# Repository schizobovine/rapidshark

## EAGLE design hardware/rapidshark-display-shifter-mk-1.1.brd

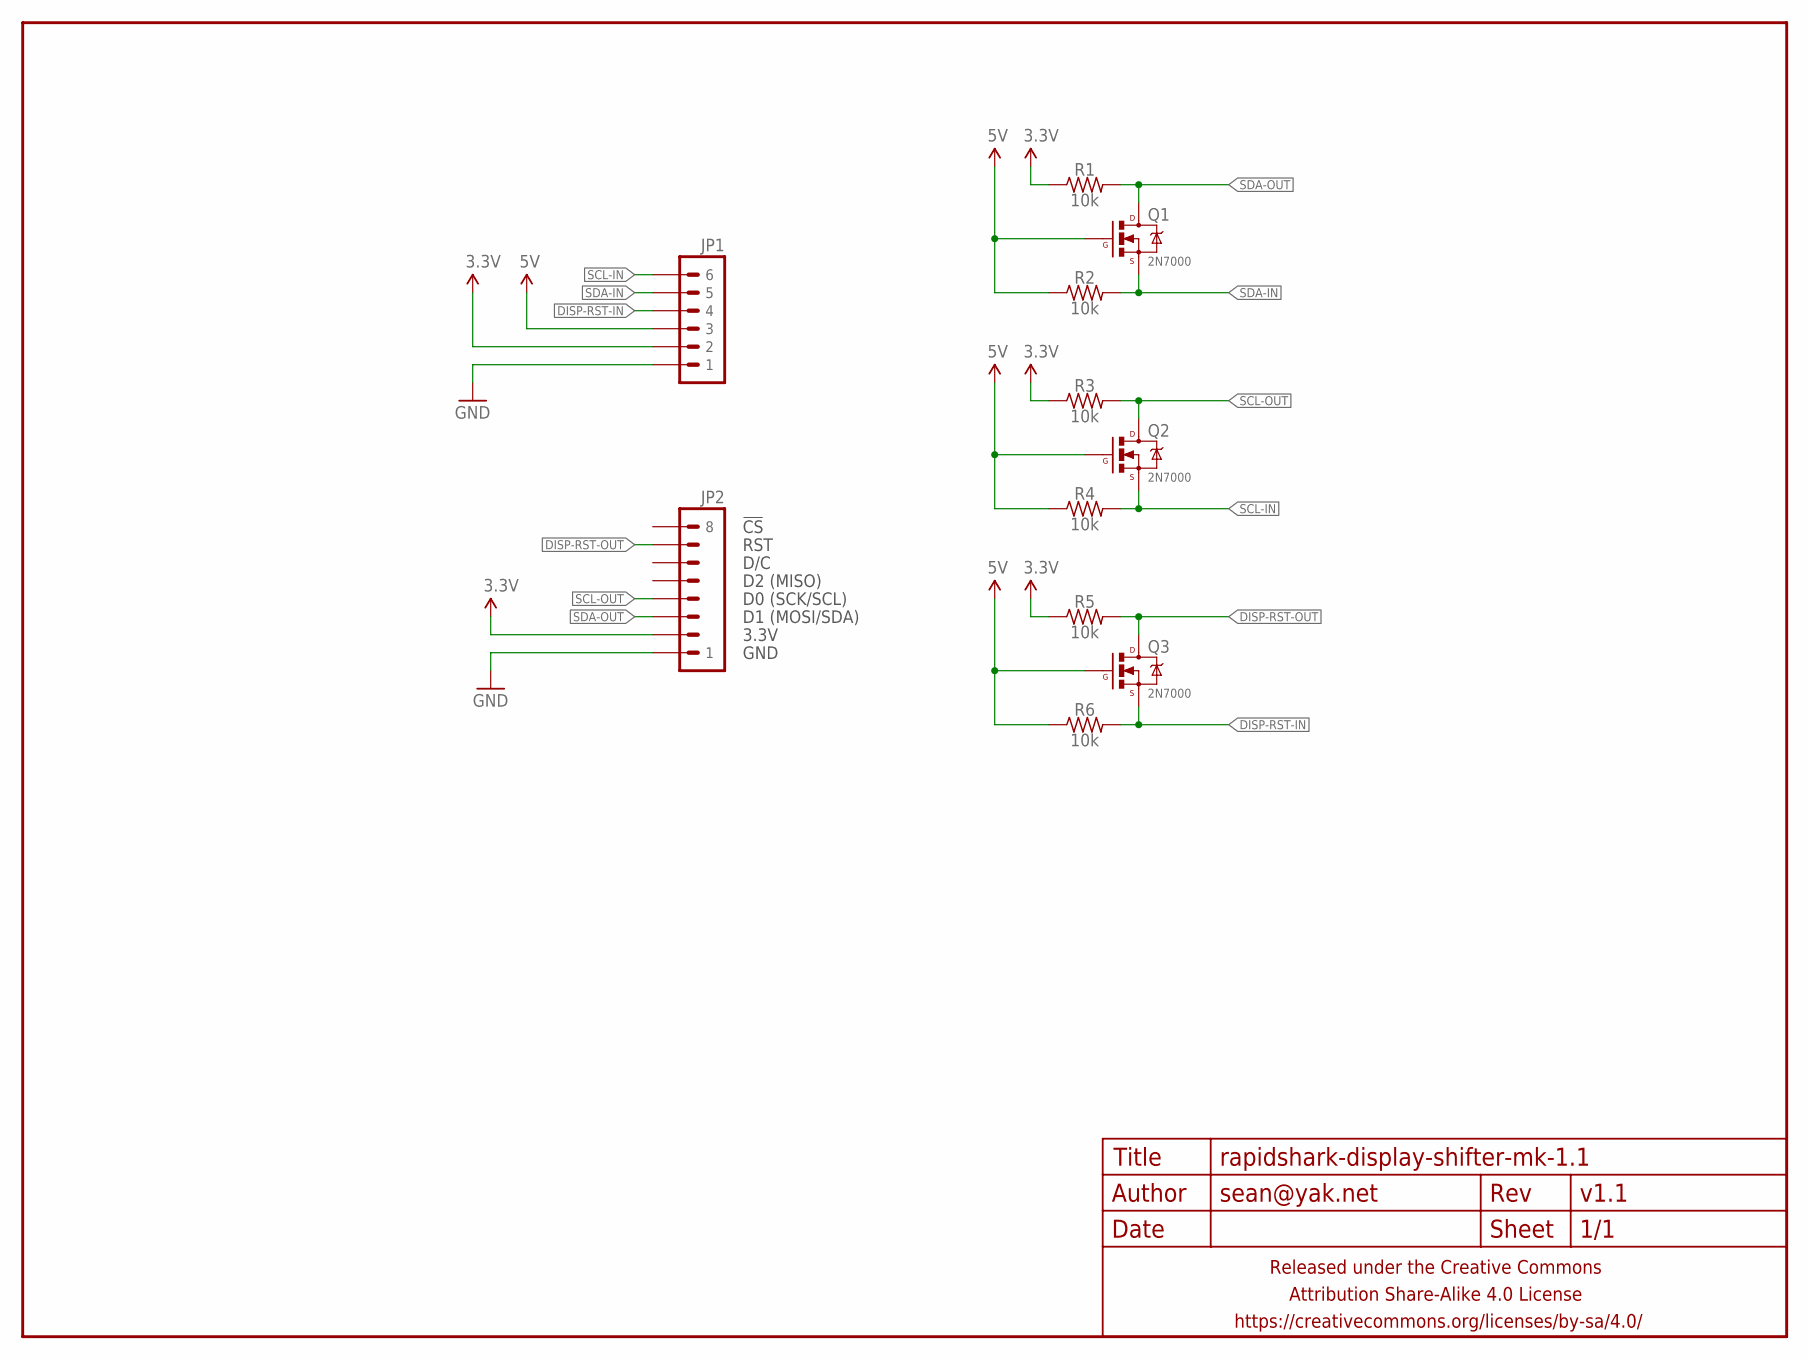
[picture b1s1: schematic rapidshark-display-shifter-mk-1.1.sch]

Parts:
FRAME1: FRAME-LETTERNO_PACKAGE; DUMMY
JP1: M06JST-PH-PTH-VERT; JST-6-PH-VERT-PTH
JP2: M081X08; 1X08
Q1, Q2, Q3: 2N7000; TO-92-AMMO
R1, R2, R3, R4, R5, R6: 10k; RESISTOR-AXIAL-PTH-5.08MM

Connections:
3.3V: JP1.2, JP2.2, R1.P$1 (1), R3.P$1 (1), R5.P$1 (1)
5V: JP1.3, Q1.2 (G), Q2.2 (G), Q3.2 (G), R2.P$1 (1), R4.P$1 (1), R6.P$1 (1)
DISP-RST-IN: JP1.4, Q3.1 (S), R6.P$2 (2)
DISP-RST-OUT: JP2.7, Q3.3 (D), R5.P$2 (2)
GND: JP1.1, JP2.1
SCL-IN: JP1.6, Q2.1 (S), R4.P$2 (2)
SCL-OUT: JP2.4, Q2.3 (D), R3.P$2 (2)
SDA-IN: JP1.5, Q1.1 (S), R2.P$2 (2)
SDA-OUT: JP2.3, Q1.3 (D), R1.P$2 (2)

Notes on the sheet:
GND
3.3V
D1 (MOSI/SDA)
D0 (SCK/SCL)
D2 (MISO)
D/C
RST
!CS

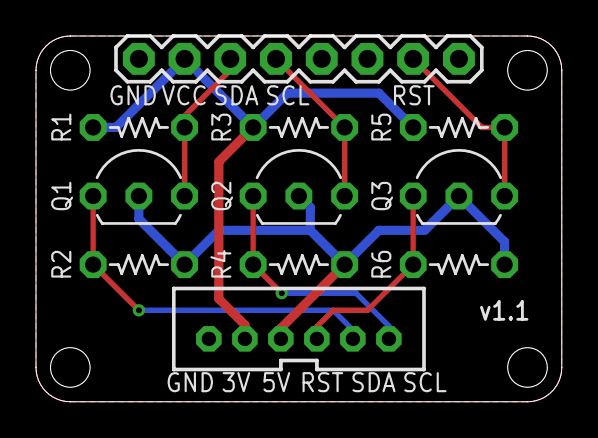
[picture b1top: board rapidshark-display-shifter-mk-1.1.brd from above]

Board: 2 copper layers, 29.2 x 20.3 mm, 12 parts (1 on the bottom side), 9 nets.

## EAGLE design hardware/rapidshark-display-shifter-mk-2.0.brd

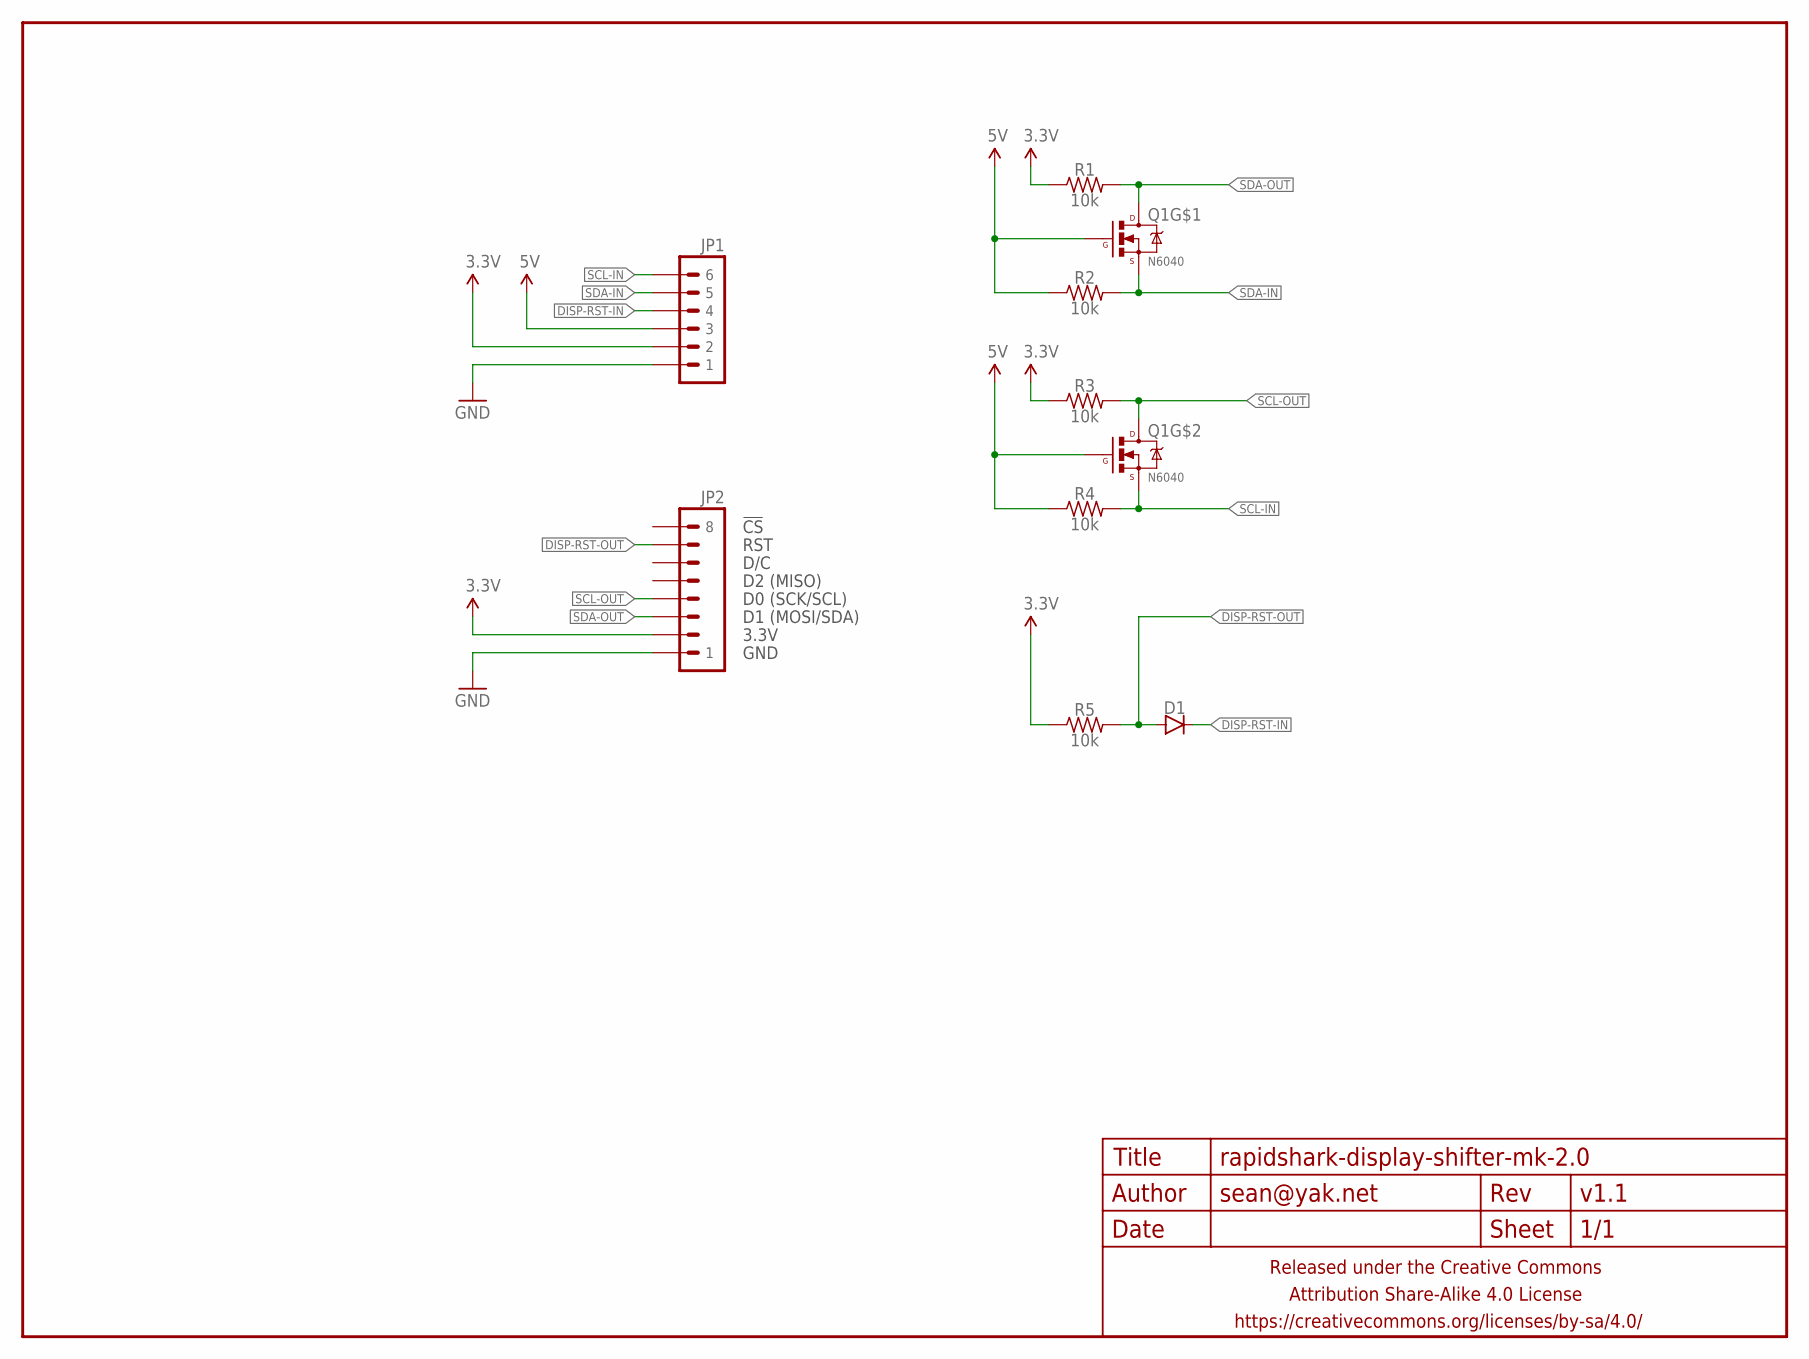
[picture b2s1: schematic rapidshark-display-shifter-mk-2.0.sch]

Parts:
D1: DIODESMA; SMA-DIODE
FRAME1: FRAME-LETTERNO_PACKAGE; DUMMY
JP1: M06JST-PH-PTH-VERT; JST-6-PH-VERT-PTH
JP2: M081X08; 1X08
Q1: N6040; SO08
R1, R2, R3, R4, R5: 10k; R0805

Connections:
3.3V: JP1.2, JP2.2, R1.1, R3.1, R5.1
5V: JP1.3, Q1.2 (G), Q1.4 (G), R2.1, R4.1
DISP-RST-IN: D1.C, JP1.4
DISP-RST-OUT: D1.A, JP2.7, R5.2
GND: JP1.1, JP2.1
SCL-IN: JP1.6, Q1.3 (S), R4.2
SCL-OUT: JP2.4, Q1.5 (D), Q1.6 (D), R3.2
SDA-IN: JP1.5, Q1.1 (S), R2.2
SDA-OUT: JP2.3, Q1.7 (D), Q1.8 (D), R1.2

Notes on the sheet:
GND
3.3V
D1 (MOSI/SDA)
D0 (SCK/SCL)
D2 (MISO)
D/C
RST
!CS

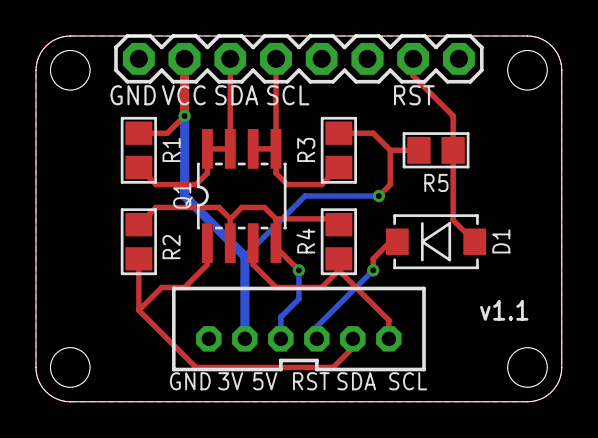
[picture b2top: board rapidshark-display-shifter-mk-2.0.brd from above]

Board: 2 copper layers, 29.2 x 20.3 mm, 10 parts (1 on the bottom side), 9 nets.

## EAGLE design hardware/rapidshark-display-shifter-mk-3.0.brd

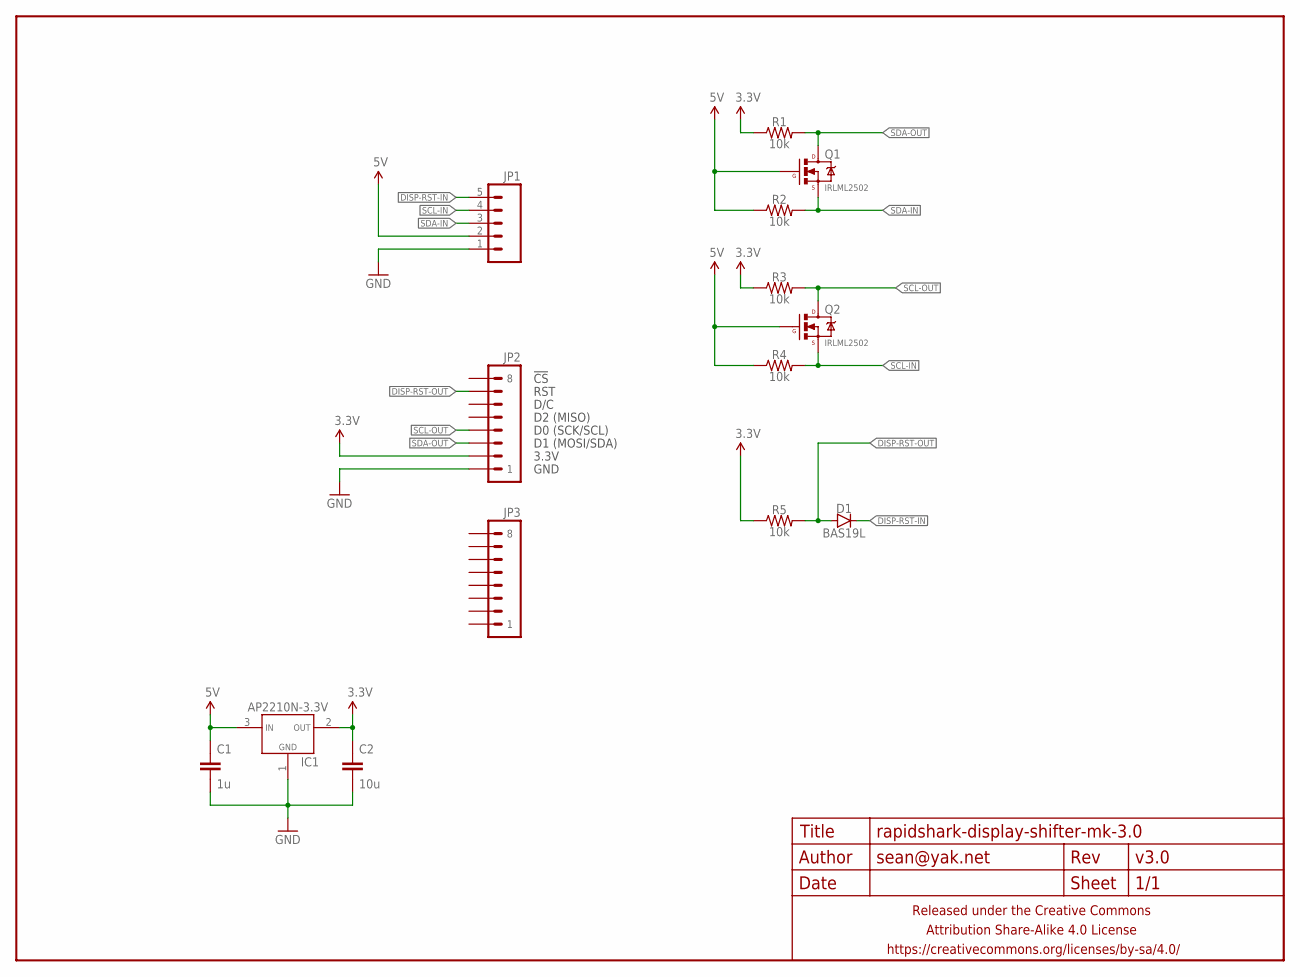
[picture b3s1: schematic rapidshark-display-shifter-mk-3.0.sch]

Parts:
C1: 1u; C0805
C2: 10u; C0805
D1: BAS19L; SOT23
FRAME1: FRAME-LETTERNO_PACKAGE; DUMMY
IC1: AP2210N-3.3V; SOT23
JP1: M05PTH-CENTERED; 1X05_PTH_CENTERED
JP2, JP3: M081X08; 1X08
Q1, Q2: IRLML2502; SOT23
R1, R2, R3, R4, R5: 10k; R0603

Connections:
3.3V: C2.1, IC1.2 (VOUT), JP2.2, R1.1, R3.1, R5.1
5V: C1.1, IC1.3 (VIN), JP1.2, Q1.1 (G), Q2.1 (G), R2.1, R4.1
DISP-RST-IN: D1.3 (C), JP1.5
DISP-RST-OUT: D1.1 (A), JP2.7, R5.2
GND: C1.2, C2.2, IC1.1 (GND), JP1.1, JP2.1
SCL-IN: JP1.4, Q2.2 (S), R4.2
SCL-OUT: JP2.4, Q2.3 (D), R3.2
SDA-IN: JP1.3, Q1.2 (S), R2.2
SDA-OUT: JP2.3, Q1.3 (D), R1.2

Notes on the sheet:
GND
3.3V
D1 (MOSI/SDA)
D0 (SCK/SCL)
D2 (MISO)
D/C
RST
!CS

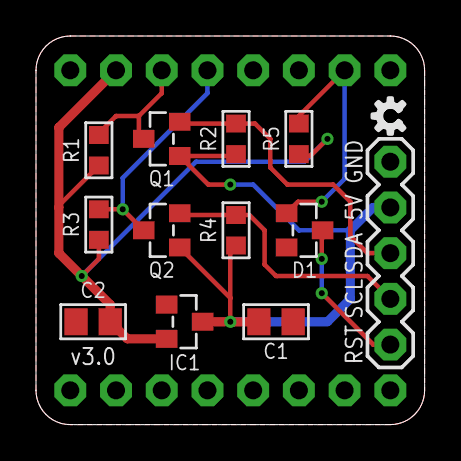
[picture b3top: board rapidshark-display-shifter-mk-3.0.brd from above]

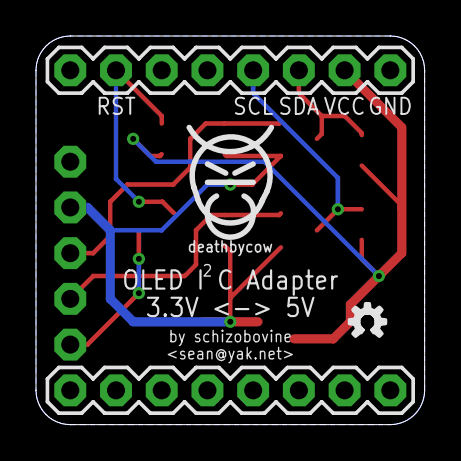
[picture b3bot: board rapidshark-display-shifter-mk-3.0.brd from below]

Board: 2 copper layers, 21.6 x 21.6 mm, 18 parts (5 on the bottom side), 9 nets.

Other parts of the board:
U$1: COW_SMALL
U$2, U$3: OSHWLOGO_TINY_SILKONLY

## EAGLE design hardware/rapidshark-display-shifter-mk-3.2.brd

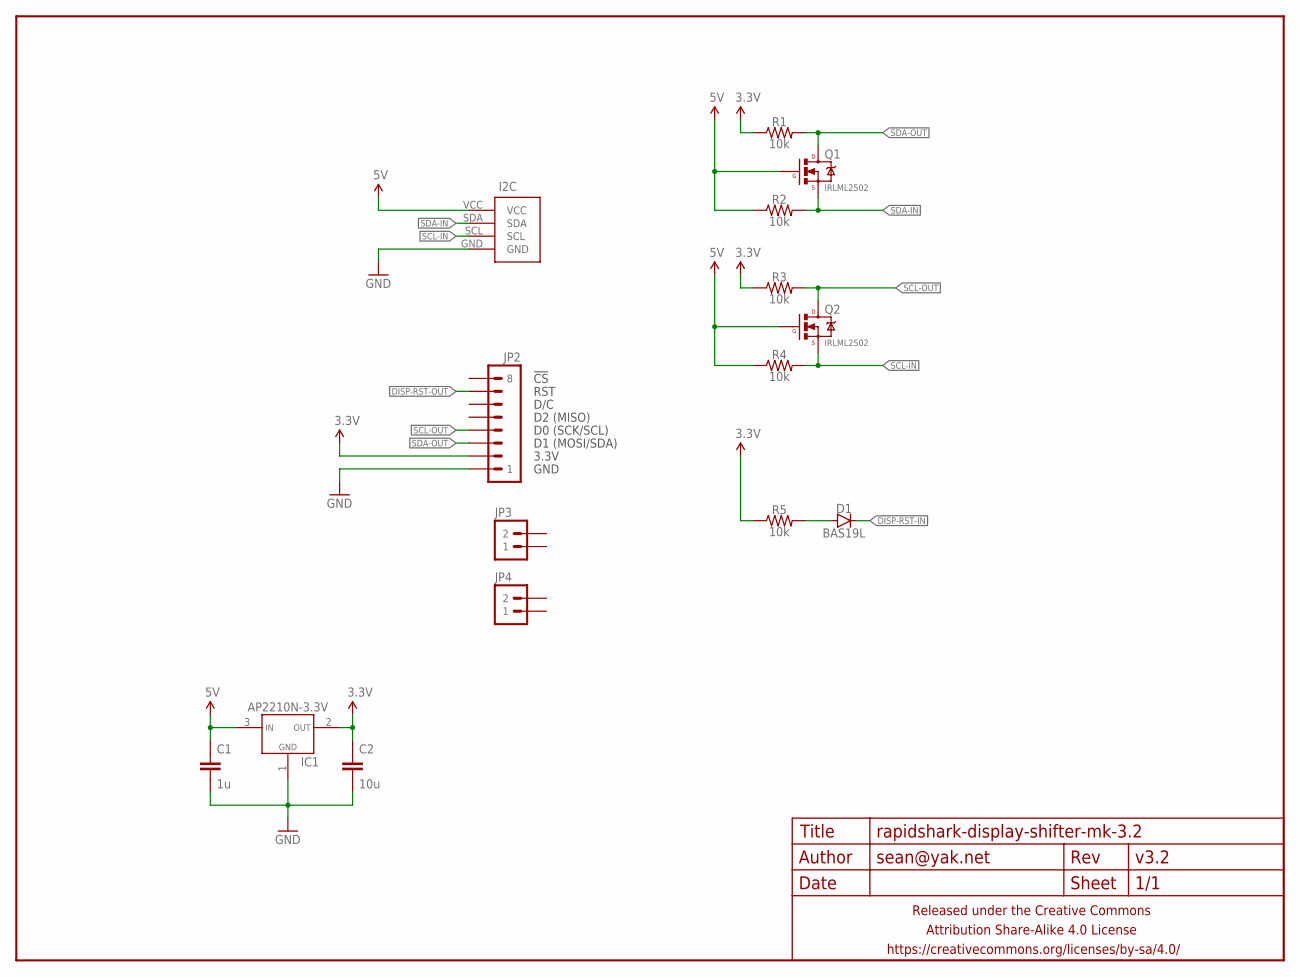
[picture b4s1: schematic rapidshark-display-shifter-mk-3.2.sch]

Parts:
C1: 1u; C0805
C2: 10u; C0805
D1: BAS19L; SOT23
FRAME1: FRAME-LETTERNO_PACKAGE; DUMMY
I2C: M04-I2CPTH-0.1IN-CENTERED-FLIPPED; 1X04-PTH-VERT-I2C-CENTERED-FLIPPED
IC1: AP2210N-3.3V; SOT23
JP2: M081X08; 1X08
JP3, JP4: M021X02_NO_SILK; 1X02_NO_SILK
Q1, Q2: IRLML2502; SOT23
R1, R2, R3, R4, R5: 10k; R0603

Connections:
3.3V: C2.1, IC1.2 (VOUT), JP2.2, R1.1, R3.1, R5.1
5V: C1.1, I2C.VCC, IC1.3 (VIN), Q1.1 (G), Q2.1 (G), R2.1, R4.1
DISP-RST-IN: D1.3 (C)
DISP-RST-OUT: JP2.7
GND: C1.2, C2.2, I2C.GND, IC1.1 (GND), JP2.1
unnamed: D1.1 (A), R5.2
SCL-IN: I2C.SCL, Q2.2 (S), R4.2
SCL-OUT: JP2.4, Q2.3 (D), R3.2
SDA-IN: I2C.SDA, Q1.2 (S), R2.2
SDA-OUT: JP2.3, Q1.3 (D), R1.2

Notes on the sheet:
GND
3.3V
D1 (MOSI/SDA)
D0 (SCK/SCL)
D2 (MISO)
D/C
RST
!CS

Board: 2 copper layers, 19 parts (4 on the bottom side), 8 nets, no tracks yet.

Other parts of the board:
U$1: COW_SMALL
U$2, U$3: OSHWLOGO_TINY_SILKONLY

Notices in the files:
parts and their libraries:
A_butts: Released under the Creative Commons Attribution Share-Alike 4.0 License
A_butts: https://creativecommons.org/licenses/by-sa/4.0
A_butts: Released under the Creative Commons
